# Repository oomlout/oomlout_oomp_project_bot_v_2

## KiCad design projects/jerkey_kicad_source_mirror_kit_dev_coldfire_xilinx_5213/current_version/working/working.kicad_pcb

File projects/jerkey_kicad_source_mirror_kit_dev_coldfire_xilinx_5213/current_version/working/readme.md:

# kicad_source_mirror
 
## summary 
* id: jerkey_kicad_source_mirror_kit_dev_coldfire_xilinx_5213
* user: jerkey
* name: kicad_source_mirror
* board: kit_dev_coldfire_xilinx_5213
* repo: https://github.com/jerkey/kicad-source-mirror
* src_file_repo_kicad_pcb: demos/kit-dev-coldfire-xilinx_5213/kit-dev-coldfire-xilinx_5213.kicad_pcb
* src_file_repo_kicad_pcb_link: https://github.com/jerkey/kicad-source-mirror/tree/master/demos/kit-dev-coldfire-xilinx_5213/kit-dev-coldfire-xilinx_5213.kicad_pcb

* src_file_repo_sch: demos/interf_u/interf_u.sch
* src_file_repo_sch_link: https://github.com/jerkey/kicad-source-mirror/tree/master/demos/interf_u/interf_u.sch
* full details link: https://github.com/oomlout/oomlout_oomp_project_bot_v_2/tree/main/projects/jerkey_kicad_source_mirror_kit_dev_coldfire_xilinx_5213/current_version/working

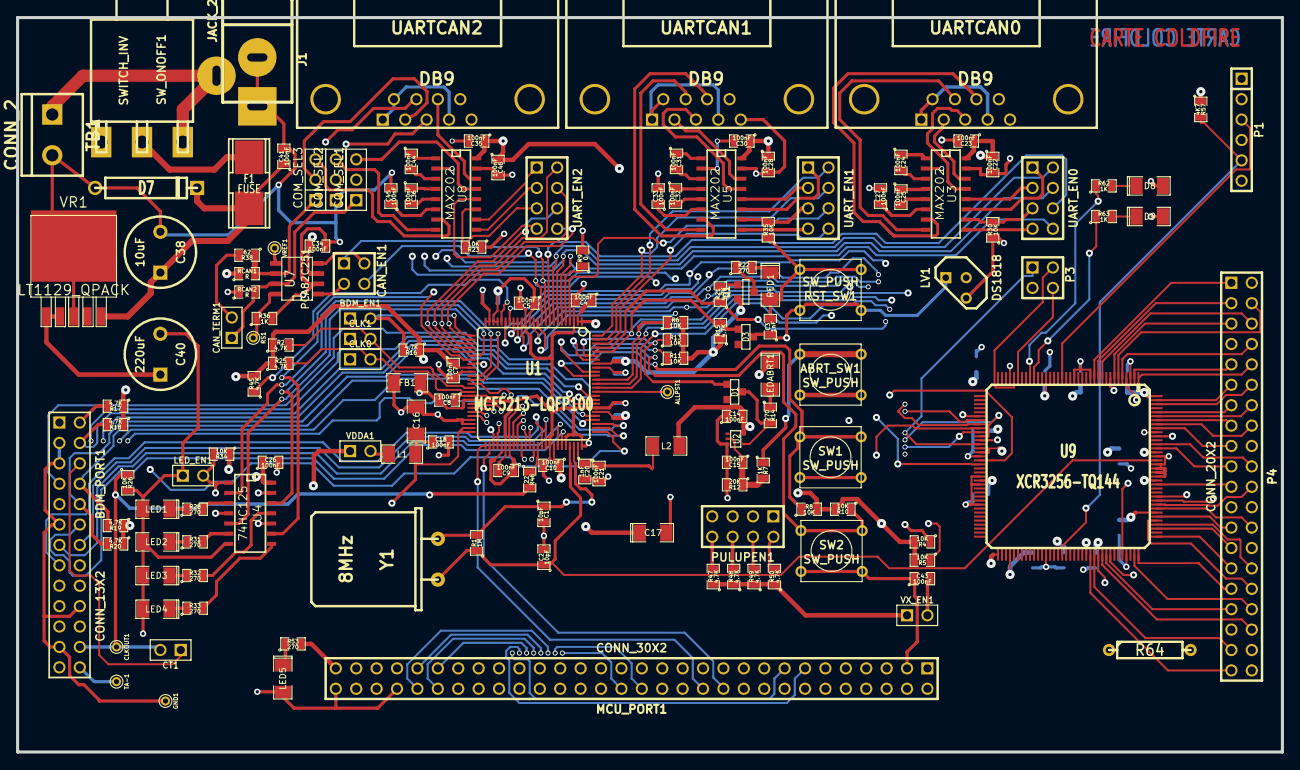
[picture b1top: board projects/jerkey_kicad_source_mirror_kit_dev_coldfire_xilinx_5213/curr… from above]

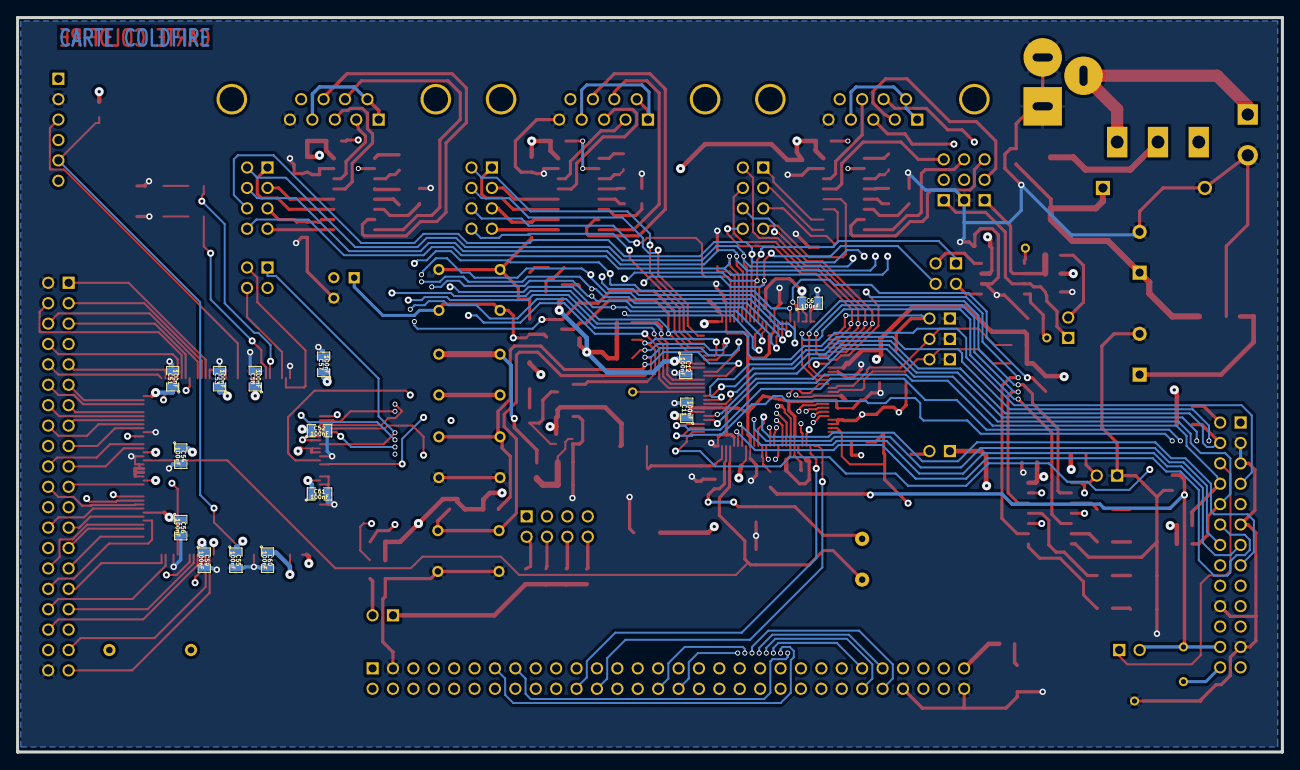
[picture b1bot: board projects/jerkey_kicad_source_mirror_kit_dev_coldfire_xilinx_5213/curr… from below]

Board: 4 copper layers, 157.5 x 91.4 mm, 162 parts (14 on the bottom side), 209 nets.

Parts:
ABRT_SW1: SW_PUSH; SW_PUSH_SMALL
ALLPST1: CONN_1; PINTST
BDM_EN1: JUMPER; PIN_ARRAY_2X1
BDM_PORT1: CONN_13X2; pin_array_13x2
C1, C2: 10pF; SM0805
C3, C20: 1nF; SM0805
C4, C5, C6, C7, C8, C9, C10, C11, C12, C14, C15, C18, C21, C22, C23, C24, C25, C26, C27, C28, C30, C31, C32, C33, C34, C35, C36, C41, C43, C44, C45, C46, C51, C52, C53, C54, C55, C56, C57, C58, C59, C60, C61: 100nF; SM0805
C16: 10uF; SM1206POL
C17: 100uF; SM1206POL
C38: 10uF; C2V8
C40: 220uF; C2V8
CAN_EN1: CONN_2X2; PIN_ARRAY_2X2
CAN_TERM1: JUMPER; PIN_ARRAY_2X1
CLK0, CLK1: JUMPER; PIN_ARRAY_2X1
CLKOUT1: CONN_1; PINTST
COM_SEL1, COM_SEL2, COM_SEL3: CONN_3; PIN_ARRAY_3X1
CT1: JUMPER; PIN_ARRAY_2X1
D1, D3: BAT54; ST23AK#1
D7: 1N4004; D5
D8, D9: LED; SM1206POL
F1: FUSE; FSUPCMS
FB1: BEAD; SM1206
GND1: CONN_1; PINTST
J1: JACK_2P; JACK_ALIM
L1, L2: 10uH; SM1206
LED1, LED2, LED3, LED4, LED5: LED; SM1206POL
LEDABRT1: RED; SM1206POL
LED_EN1: JUMPER; PIN_ARRAY_2X1
LV1: DS1818; TO92-INVERT
MCU_PORT1: CONN_30X2; PIN_ARRAY_30X2
P1: CONN_6; PIN_ARRAY-6X1
P3: CONN_2X2; PIN_ARRAY_2X2
P4: CONN_20X2; PIN_ARRAY_20X2
PULUPEN1: CONN_4X2; pin_array_4x2
Q1: 3906; SOT23EBC
R1: 1M; SM0805
R2, R15, R16, R17, R18, R19, R20, R21, R25, R45, R47, R48, R49, R50: 4,7K; SM0805
R4, R5, R6, R8, R10, R11, R13, R23, R26, R30, R34, R35: 10K; SM0805
R7, R36, R62, R63: 1K; SM0805
R9: 0; SM0805
R12: 20K; SM0805
R14, R22, R28, R31, R32, R33, R53: 270; SM0805
R38: 62; SM0805
R46: 22; SM0805
R57: 4K7; SM0805
R64: 3,3; R4
RCAN1, RCAN2: R; SM0805
RED1: LED_RESET1; SM1206POL
RS1: CONN_1; PINTST
RST_SW1: SW_PUSH; SW_PUSH_SMALL
SW1, SW2: SW_PUSH; SW_PUSH_SMALL
SW_ONOFF1: SWITCH_INV; SW_SPDT
TA-1: CONN_1; PINTST
TB1: CONN_2; bornier2
U1: MCF5213-LQFP100; VQFP100
U2: 74AHC1G14; SOT353
U3, U5, U8: MAX202; SO16E
U4: 74HC125; SO14E
U7: PCA82C251; SO8E
U9: XCR3256-TQ144; TQFP144
UARTCAN0, UARTCAN1, UARTCAN2: DB9; DB9FC
UART_EN0, UART_EN1, UART_EN2: CONN_4X2; pin_array_4x2
VDDA1: JUMPER; PIN_ARRAY_2X1
VR1: LT1129_QPACK; DPAK5
VREF1: CONN_1; PINTST
VX_EN1: JUMPER; PIN_ARRAY_2X1
Y1: 8MHz; HC-18UH

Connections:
/ALLPST: ALLPST1.1, U1.86
/AN0: MCU_PORT1.10, U1.43
/AN1: MCU_PORT1.12, U1.44
/AN2: MCU_PORT1.14, U1.45
/AN3: MCU_PORT1.16, U1.46
/AN4: MCU_PORT1.18, U1.54
/AN5: MCU_PORT1.20, U1.53
/AN6: MCU_PORT1.22, U1.52
/AN7: MCU_PORT1.24, U1.51
/BKPT-: BDM_PORT1.2, R17.2, U1.76
/CLKIN/EXTAL: C1.1, R1.2, U1.73, Y1.1
/CLKMOD0: CLK0.2, R25.2, U1.40
/CLKMOD1: CLK1.2, R2.2, U1.39
/DDAT0: BDM_PORT1.19, U1.77
/DDAT1: BDM_PORT1.18, U1.78
/DDAT2: BDM_PORT1.17, U1.83
/DDAT3: BDM_PORT1.16, U1.84
/DSCLK: BDM_PORT1.4, R18.2, U1.85
/DSI: BDM_PORT1.8, R19.2, U1.79
/DSO: BDM_PORT1.10, R20.2, U1.80
/DTIN0: MCU_PORT1.34, U1.36, U4.2
/DTIN1: MCU_PORT1.36, U1.37, U4.5
/DTIN2: MCU_PORT1.38, U1.31, U4.12
/DTIN3: MCU_PORT1.40, U1.32, U4.9
/GPT0: MCU_PORT1.49, U1.58
/GPT1: MCU_PORT1.50, U1.59
/GPT2: MCU_PORT1.51, U1.61
/GPT3: MCU_PORT1.52, U1.62
/IRQ-4: MCU_PORT1.33, R8.1, SW1.1, U1.90
/IRQ-5: MCU_PORT1.35, R10.1, SW2.1, U1.91
/IRQ-6: MCU_PORT1.37, R11.1, U1.94
/IRQ-7: D1.1, MCU_PORT1.39, R13.1, U1.95
/JTAG_EN: BDM_EN1.2, R16.2, U1.26
/PST0: BDM_PORT1.15, U1.65
/PST1: BDM_PORT1.14, U1.66
/PST2: BDM_PORT1.13, U1.69
/PST3: BDM_PORT1.12, U1.70
/QSPI_CS0: MCU_PORT1.23, PULUPEN1.3, U1.20
/QSPI_CS3: MCU_PORT1.29, U1.12
/TCLK: BDM_PORT1.24, CLKOUT1.1, CT1.2, R26.1, R46.2
/VDDPLL: C20.1, C21.1, L2.2, U1.74
/inout_user/CANRX: CAN_EN1.4, MCU_PORT1.28, PULUPEN1.7, U1.11
/inout_user/CANTX: CAN_EN1.1, MCU_PORT1.26, PULUPEN1.5, U1.10
/inout_user/CAN_H: CAN_TERM1.1, COM_SEL1.1, RCAN2.2, U7.7
/inout_user/CAN_L: COM_SEL3.1, R38.1, RCAN1.2, U7.6
/inout_user/CTS0: U3.8, UARTCAN0.7
/inout_user/CTS1: U5.8, UARTCAN1.7
/inout_user/CTS2/CANH: COM_SEL1.2, UARTCAN2.7
/inout_user/PWM1: MCU_PORT1.13, U1.38
/inout_user/PWM3: MCU_PORT1.15, U1.33
/inout_user/PWM5: MCU_PORT1.30, U1.60
/inout_user/PWM7: MCU_PORT1.32, U1.63
/inout_user/QSPI_DIN: MCU_PORT1.19, U1.16, U9.46
/inout_user/QSPI_DOUT: MCU_PORT1.17, U1.17, U9.47
/inout_user/QSPI_SCLK: MCU_PORT1.21, PULUPEN1.1, U1.18, U9.48
/inout_user/RCON-: MCU_PORT1.53, R45.1, U1.21
/inout_user/RSTI-: BDM_PORT1.7, D3.1, MCU_PORT1.6, R15.2, U1.96
/inout_user/RTS0: U3.7, UARTCAN0.8
/inout_user/RTS0-: MCU_PORT1.4, R21.1, U1.97
/inout_user/RTS1: U5.7, UARTCAN1.8
/inout_user/RTS2: U8.14, UARTCAN2.8
/inout_user/RXD0: U3.13, UARTCAN0.3
/inout_user/RXD1: U5.13, UARTCAN1.3
/inout_user/RXD2: COM_SEL2.2, UARTCAN2.3
/inout_user/RxD_CAN: CAN_EN1.2, U7.4
/inout_user/TXD0: U3.14, UARTCAN0.2
/inout_user/TXD1: U5.14, UARTCAN1.2
/inout_user/TXD2/CANL: COM_SEL3.2, UARTCAN2.2
/inout_user/TxD_CAN: CAN_EN1.3, U7.1
/inout_user/UCTS0: MCU_PORT1.44, U1.6, UART_EN0.8
/inout_user/UCTS1: MCU_PORT1.11, P3.1, U1.98, U9.49, UART_EN1.8
/inout_user/UCTS2: MCU_PORT1.48, U1.27, UART_EN2.8
/inout_user/URTS0: MCU_PORT1.42, U1.9, UART_EN0.6
/inout_user/URTS1: MCU_PORT1.9, P3.3, U1.4, U9.53, UART_EN1.6
/inout_user/URTS2: MCU_PORT1.46, U1.30, UART_EN2.6
/inout_user/URXD0: MCU_PORT1.43, U1.7, UART_EN0.4
/inout_user/URXD1: MCU_PORT1.7, U1.100, UART_EN1.4
/inout_user/URXD2: MCU_PORT1.47, U1.28, UART_EN2.4
/inout_user/UTXD0: MCU_PORT1.41, U1.8, UART_EN0.2
/inout_user/UTXD1: MCU_PORT1.5, U1.99, UART_EN1.2
/inout_user/UTXD2: MCU_PORT1.45, U1.29, UART_EN2.2
/inout_user/VCCA: C16.1, C18.1, L1.2, MCU_PORT1.55, MCU_PORT1.57, U1.49, U1.50
/xilinx/+3,3V_OUT: P4.38, R64.2
/xilinx/GLCK2: C2.1, R1.1, U1.72, U9.128, Y1.2
/xilinx/IRQ-1: MCU_PORT1.2, R4.1, U1.87, U9.42
/xilinx/IRQ-2: MCU_PORT1.8, R5.1, U1.88, U9.43
/xilinx/IRQ-3: MCU_PORT1.31, R6.1, U1.89, U9.44
/xilinx/LED_TEST1: R62.1, U9.28
/xilinx/LED_TEST2: R63.1, U9.27
/xilinx/QSPI_CS1: MCU_PORT1.25, U1.19, U9.54
/xilinx/QSPI_CS2: MCU_PORT1.27, U1.13, U9.45
/xilinx/TCK: P1.5, R57.2, U9.89
/xilinx/TDI: P1.4, U9.4
/xilinx/TDO: P1.6, U9.104
/xilinx/TMS: P1.3, U9.20
/xilinx/XIL_D0: P4.1, U9.12
/xilinx/XIL_D1: P4.3, U9.11
/xilinx/XIL_D2: P4.5, U9.7
/xilinx/XIL_D3: P4.7, U9.8
/xilinx/XIL_D4: P4.9, U9.2
/xilinx/XIL_D5: P4.11, U9.143
/xilinx/XIL_D6: P4.13, U9.140
/xilinx/XIL_D7: P4.15, U9.138
/xilinx/XIL_D8: P4.17, U9.136
/xilinx/XIL_D9: P4.19, U9.131
/xilinx/XIL_D10: P4.21, U9.122
/xilinx/XIL_D11: P4.23, U9.119
/xilinx/XIL_D12: P4.25, U9.114
/xilinx/XIL_D13: P4.27, U9.111
/xilinx/XIL_D14: P4.29, U9.109
/xilinx/XIL_D15: P4.31, U9.108
/xilinx/XIL_D16: P4.33, U9.100
/xilinx/XIL_D17: P4.35, U9.101
/xilinx/XIL_D18: P4.37, U9.97
/xilinx/XIL_D19: P4.39, U9.96
/xilinx/XIL_D20: P4.4, U9.6
/xilinx/XIL_D21: P4.6, U9.10
/xilinx/XIL_D22: P4.8, U9.5
/xilinx/XIL_D23: P4.10, U9.1
/xilinx/XIL_D24: P4.12, U9.142
/xilinx/XIL_D25: P4.14, U9.139
/xilinx/XIL_D26: P4.16, U9.137
/xilinx/XIL_D27: P4.18, U9.134
/xilinx/XIL_D28: P4.20, U9.132
/xilinx/XIL_D29: P4.22, U9.117
/xilinx/XIL_D30: P4.24, U9.118
/xilinx/XIL_D31: P4.26, U9.116
/xilinx/XIL_D32: P4.28, U9.98
/xilinx/XIL_D33: P4.30, U9.112
/xilinx/XIL_D34: P4.32, U9.113
/xilinx/XIL_D35: P4.34, U9.107
/xilinx/XIL_D36: P4.36, U9.99
GND: BDM_EN1.1, BDM_PORT1.3, BDM_PORT1.5, BDM_PORT1.11, BDM_PORT1.20, BDM_PORT1.23, C1.2, C2.2, C3.2, C4.2, C5.2, C6.2, C7.2, C8.2, C9.2, C10.2, C11.2, C12.2, C14.1, C15.2, C17.2, C20.2, C21.2, C22.2, C26.2, C27.2, C28.2, C33.2, C34.2, C38.2, C40.2, C41.2, C43.1, C45.2, C46.2, C51.2, C52.2, C53.2, C54.2, C55.2, C56.2, C57.2, C58.2, C59.2, C60.2, C61.2, CLK0.1, CLK1.1, COM_SEL2.1, D7.1, D8.2, D9.2, FB1.1, GND1.1, J1.1, J1.2, LED1.2, LED2.2, LED3.2, LED4.2, LED5.2, LED_EN1.1, LV1.3, MCU_PORT1.3, MCU_PORT1.54, MCU_PORT1.60, P1.2, P4.2, P4.40, R9.2, R12.2, R23.1, R26.2, R30.1, R35.1, R36.2, RCAN2.1, RED1.2, RST_SW1.2, SW1.2, SW2.2, TB1.2, U1.3, U1.15, U1.24, U1.25, U1.35, U1.42, U1.56, U1.67, U1.71, U1.75, U1.82, U1.92, U2.3, U3.15, U4.7, U5.15, U7.2, U8.15, U9.3, U9.13, U9.17, U9.33, U9.52, U9.57, U9.59, U9.64, U9.85, U9.105, U9.124, U9.125, U9.126, U9.127, U9.129, U9.135, UARTCAN0.5, UARTCAN1.5, UARTCAN2.5, VR1.3
GNDA: C16.2, C18.2, FB1.2, MCU_PORT1.56, MCU_PORT1.58, U1.47, U1.48
unnamed: ABRT_SW1.1, R7.1
unnamed: BDM_PORT1.6, CT1.1
unnamed: BDM_PORT1.26, TA-1.1
unnamed: C3.1, D3.2, LV1.1, RST_SW1.1
unnamed: C15.1, R7.2, R12.1, U2.2
unnamed: C23.2, U3.2
unnamed: C24.1, U3.1
unnamed: C24.2, U3.3
unnamed: C25.1, U3.4
unnamed: C25.2, U3.5
unnamed: C27.1, U3.6
unnamed: C30.2, U5.2
unnamed: C31.1, U5.1
unnamed: C31.2, U5.3
unnamed: C32.1, U5.4
unnamed: C32.2, U5.5
unnamed: C33.1, U5.6
unnamed: C35.2, U8.2
unnamed: C36.1, U8.4
unnamed: C36.2, U8.5
unnamed: C38.1, C41.1, D7.2, F1.2, VR1.5
unnamed: C43.2, MCU_PORT1.1, VX_EN1.2
unnamed: C44.1, U8.1
unnamed: C44.2, U8.3
unnamed: C45.1, U8.6
unnamed: CAN_TERM1.2, R38.2
unnamed: COM_SEL1.3, U8.13
unnamed: COM_SEL2.3, U8.8
unnamed: COM_SEL3.3, U8.7
unnamed: D1.2, R14.2, U2.4
unnamed: D8.1, R62.2
unnamed: D9.1, R63.2
unnamed: F1.1, SW_ONOFF1.2
unnamed: J1.3, SW_ONOFF1.3, TB1.1
unnamed: L1.1, VDDA1.2
unnamed: LED1.1, R28.1
unnamed: LED2.1, R31.1
unnamed: LED3.1, R32.1
unnamed: LED4.1, R33.1
unnamed: LED5.1, R53.1
unnamed: LEDABRT1.2, R14.1
unnamed: LED_EN1.2, R34.2, U4.1, U4.4, U4.10, U4.13
unnamed: P3.2, U9.32
unnamed: P3.4, U9.31
unnamed: PULUPEN1.2, R50.2
unnamed: PULUPEN1.4, R49.2
unnamed: PULUPEN1.6, R48.2
unnamed: PULUPEN1.8, R47.2
unnamed: Q1.2, R21.2
unnamed: Q1.3, R22.1
unnamed: R9.1, U1.5
unnamed: R22.2, RED1.1
unnamed: R23.2, U8.11, UART_EN2.5
unnamed: R28.2, U4.3
unnamed: R30.2, U3.10, UART_EN0.5
unnamed: R31.2, U4.6
unnamed: R32.2, U4.11
unnamed: R33.2, U4.8
unnamed: R35.2, U5.10, UART_EN1.5
unnamed: R36.1, RS1.1, U7.8
unnamed: R46.1, U1.64
unnamed: U3.9, UART_EN0.7
unnamed: U3.11, UART_EN0.1
unnamed: U3.12, UART_EN0.3
unnamed: U5.9, UART_EN1.7
unnamed: U5.11, UART_EN1.1
unnamed: U5.12, UART_EN1.3
unnamed: U7.5, VREF1.1
unnamed: U8.9, UART_EN2.3
unnamed: U8.10, UART_EN2.1
unnamed: U8.12, UART_EN2.7
unnamed: UARTCAN0.1, UARTCAN0.4, UARTCAN0.6
unnamed: UARTCAN1.1, UARTCAN1.4, UARTCAN1.6
unnamed: UARTCAN2.1, UARTCAN2.4, UARTCAN2.6
VDD: ABRT_SW1.2, BDM_PORT1.9, BDM_PORT1.25, C4.1, C5.1, C6.1, C7.1, C8.1, C9.1, C10.1, C11.1, C12.1, C14.2, C17.1, C22.1, C23.1, C26.1, C28.1, C30.1, C34.1, C35.1, C40.1, C46.1, C51.1, C52.1, C53.1, C54.1, C55.1, C56.1, C57.1, C58.1, C59.1, C60.1, C61.1, L2.1, LEDABRT1.1, LV1.2, MCU_PORT1.59, P1.1, Q1.1, R2.1, R4.2, R5.2, R6.2, R8.2, R10.2, R11.2, R13.2, R15.1, R16.1, R17.1, R18.1, R19.1, R20.1, R25.1, R34.1, R45.2, R47.1, R48.1, R49.1, R50.1, R53.2, R57.1, R64.1, RCAN1.1, U1.1, U1.2, U1.14, U1.22, U1.23, U1.34, U1.41, U1.55, U1.57, U1.68, U1.81, U1.93, U2.5, U3.16, U4.14, U5.16, U7.3, U8.16, U9.24, U9.50, U9.51, U9.58, U9.73, U9.76, U9.95, U9.115, U9.123, U9.130, U9.144, VDDA1.1, VR1.1, VR1.2, VX_EN1.1

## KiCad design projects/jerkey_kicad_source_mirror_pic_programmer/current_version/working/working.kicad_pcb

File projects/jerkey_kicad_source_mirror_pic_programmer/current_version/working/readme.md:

# kicad_source_mirror
 
## summary 
* id: jerkey_kicad_source_mirror_pic_programmer
* user: jerkey
* name: kicad_source_mirror
* board: pic_programmer
* repo: https://github.com/jerkey/kicad-source-mirror
* src_file_repo_kicad_pcb: demos/pic_programmer/pic_programmer.kicad_pcb
* src_file_repo_kicad_pcb_link: https://github.com/jerkey/kicad-source-mirror/tree/master/demos/pic_programmer/pic_programmer.kicad_pcb

* src_file_repo_sch: demos/pic_programmer/pic_programmer.sch
* src_file_repo_sch_link: https://github.com/jerkey/kicad-source-mirror/tree/master/demos/pic_programmer/pic_programmer.sch
* full details link: https://github.com/oomlout/oomlout_oomp_project_bot_v_2/tree/main/projects/jerkey_kicad_source_mirror_pic_programmer/current_version/working

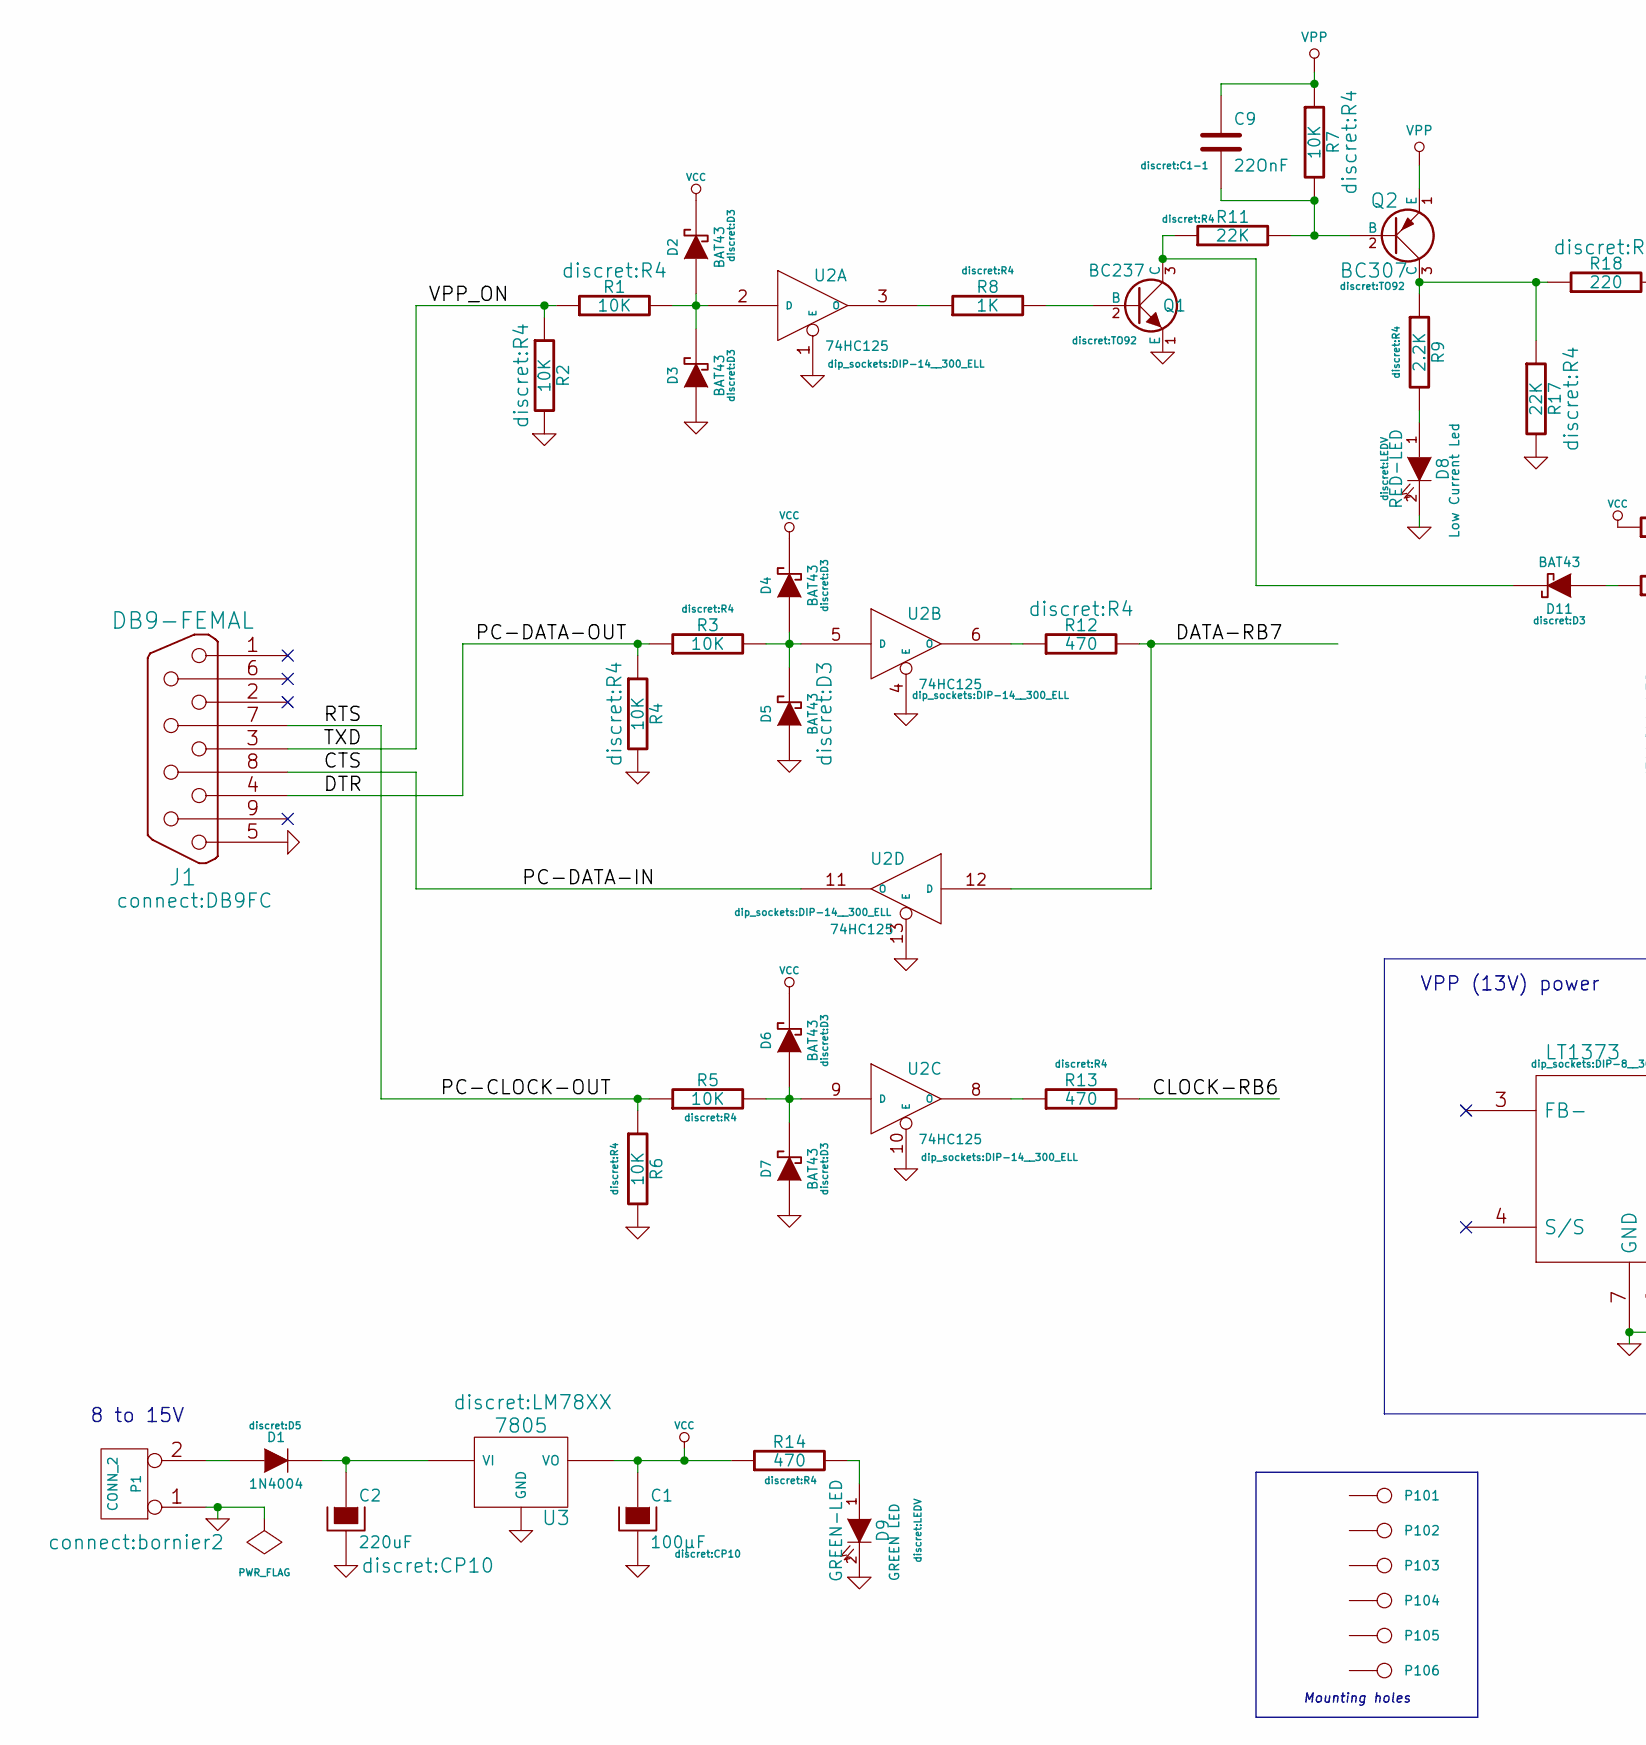
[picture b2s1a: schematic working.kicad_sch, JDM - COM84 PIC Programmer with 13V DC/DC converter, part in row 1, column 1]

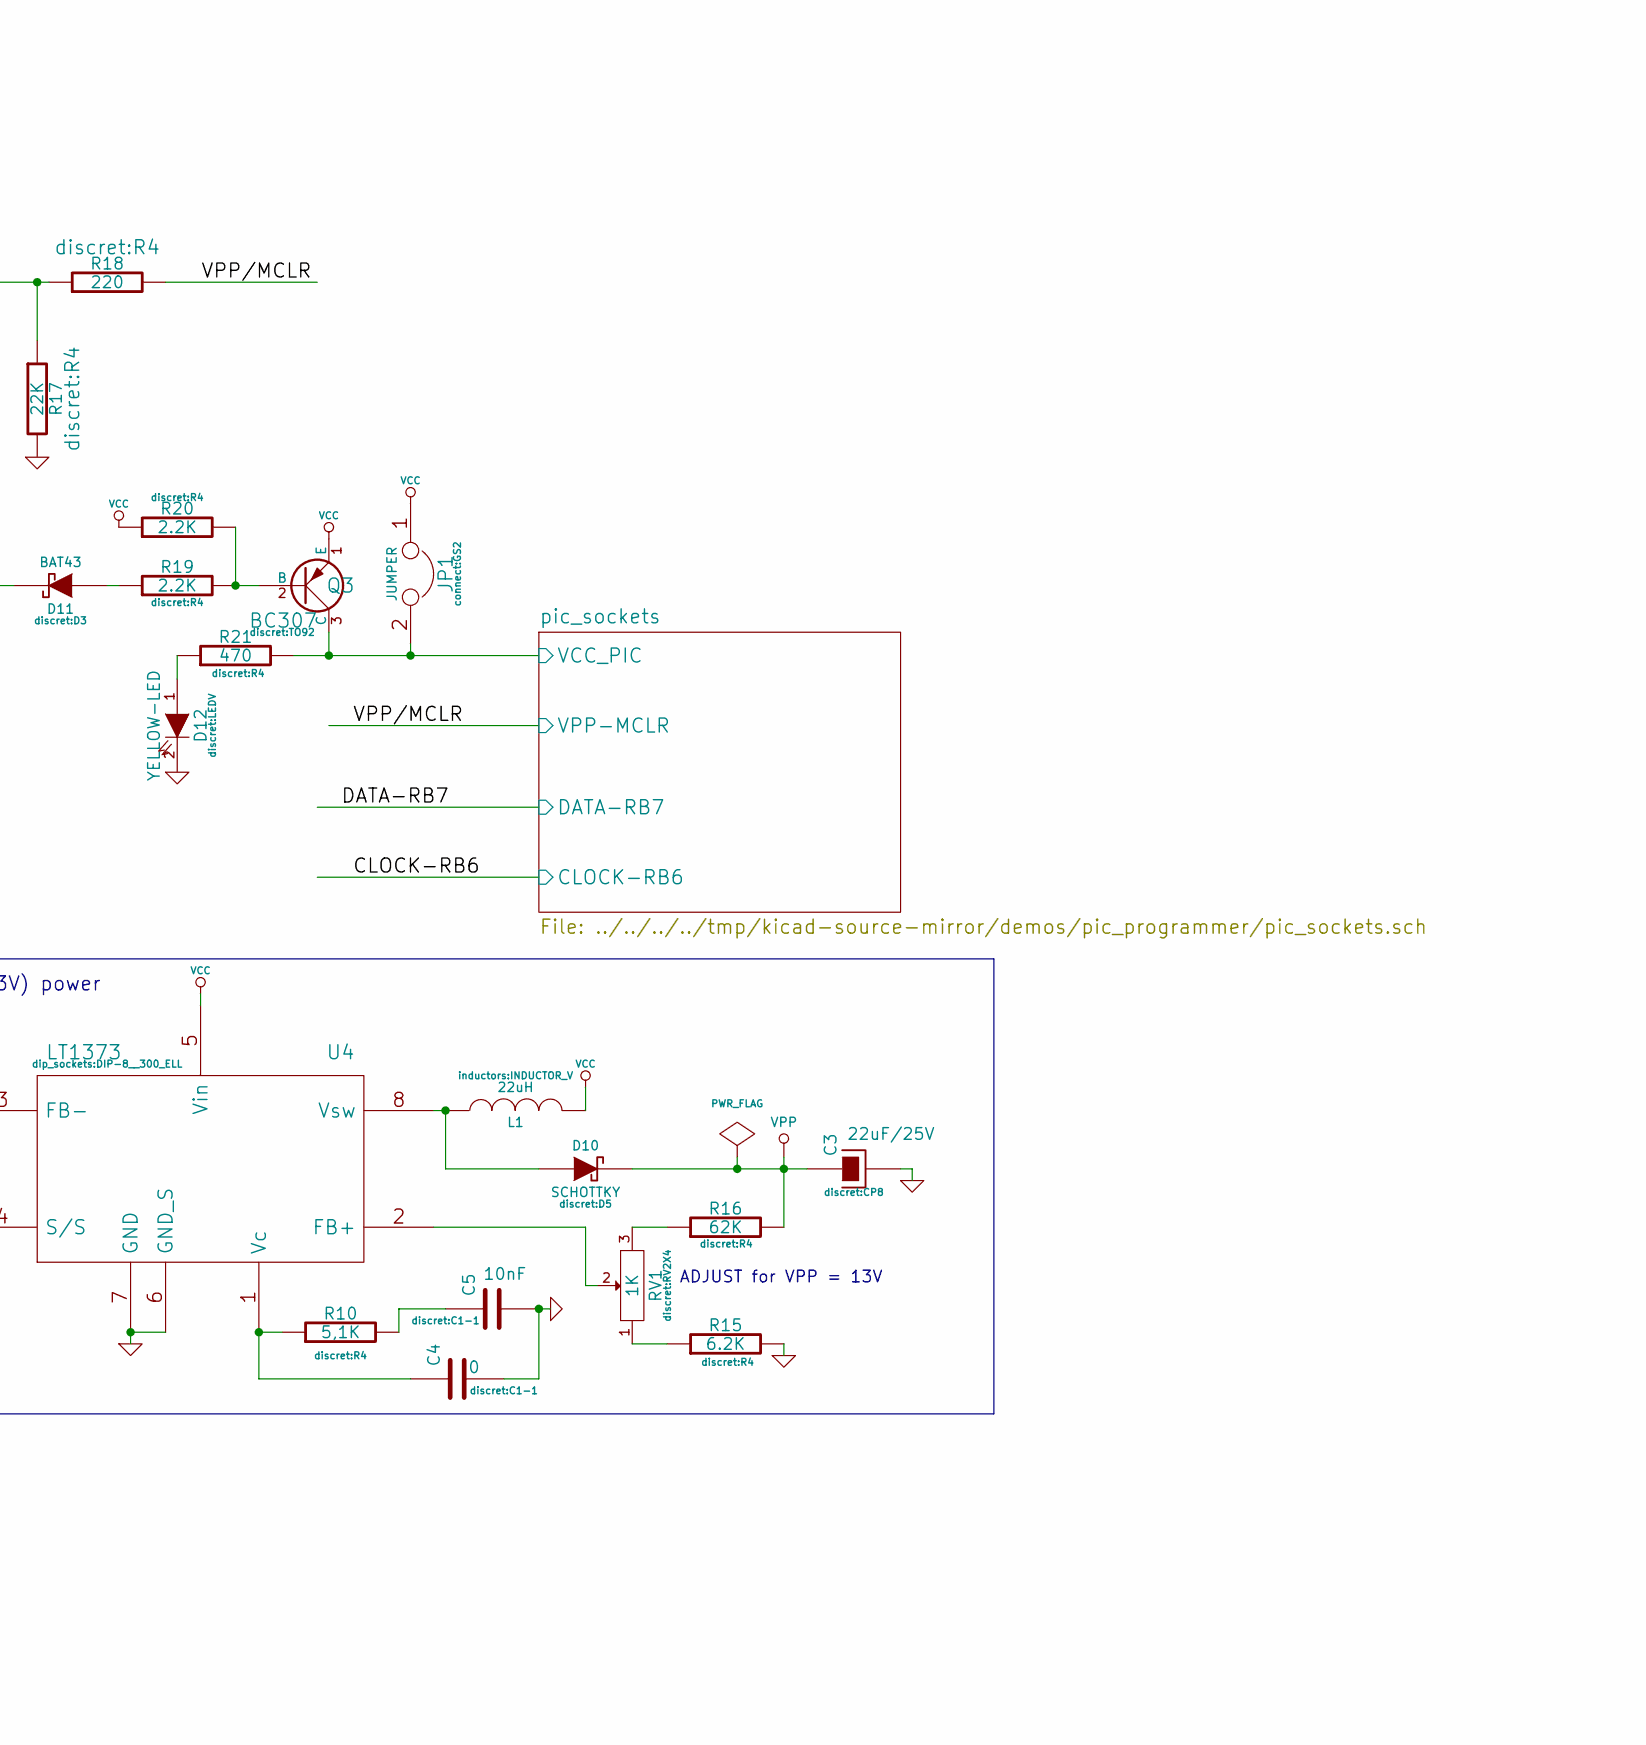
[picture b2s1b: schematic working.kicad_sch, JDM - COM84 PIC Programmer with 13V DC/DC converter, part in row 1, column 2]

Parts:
C1: 100µF; CP10
C2: 220uF; CP10
C3: 22uF/25V; CP8
C4: 0; C1-1
C5: 10nF; C1-1
C9: 22OnF; C1-1
D1: 1N4004; D5
D2, D3, D4, D5, D6, D7, D11: BAT43; D3
D8: RED-LED; LEDV
D9: GREEN-LED; LEDV
D10: SCHOTTKY; D5
D12: YELLOW-LED; LEDV
J1: DB9-FEMAL; DB9FC
JP1: JUMPER; GS2
L1: 22uH; INDUCTOR_V
P1: CONN_2; bornier2
P101, P102, P103, P104, P105, P106: CONN_1; 1pin-4
Q1: BC237; TO92
Q2, Q3: BC307; TO92
R1, R2, R3, R4, R5, R6, R7: 10K; R4
R8: 1K; R4
R9, R19, R20: 2.2K; R4
R10: 5,1K; R4
R11, R17: 22K; R4
R12, R13, R14, R21: 470; R4
R15: 6.2K; R4
R16: 62K; R4
R18: 220; R4
RV1: 1K; RV2X4
U2: 74HC125; DIP-14__300_ELL
U3: 7805; LM78XX
U4: LT1373; DIP-8__300_ELL

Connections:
/CTS: J1.8, U2.11 (O)
/DTR: J1.4, R3.1, R4.1
/PC-CLOCK-OUT: J1.7, R5.1, R6.1
/TXD: J1.3, R1.1, R2.1
/pic_sockets/CLOCK-RB6: R13.2; also elsewhere on the board
/pic_sockets/DATA-RB7: R12.2, U2.12 (D); also elsewhere on the board
/pic_sockets/VCC_PIC: JP1.2, Q3.3 (C), R21.2; also elsewhere on the board
/pic_sockets/VPP-MCLR: R18.2; also elsewhere on the board
GND: C1.2, C2.2, C3.2, C4.2, C5.2, D3.1 (A), D5.1 (A), D7.1 (A), D8.2 (K), D9.2 (K), D12.2 (K), J1.5, P1.1, Q1.1 (E), R2.2, R4.2, R6.2, R15.2, R17.2, U2.1 (E), U2.4 (E), U2.7 (GND), U2.10 (E), U2.13 (E), U3.GND, U4.6 (GND_S), U4.7 (GND); also elsewhere on the board
unnamed: C2.1, D1.2 (K), U3.VI
unnamed: C4.1, R10.1, U4.1 (Vc)
unnamed: C5.1, R10.2
unnamed: C9.2, Q2.2 (B), R7.2, R11.2
unnamed: D1.1 (A), P1.2 (PM)
unnamed: D2.1 (A), D3.2 (K), R1.2, U2.2 (D)
unnamed: D4.1 (A), D5.2 (K), R3.2, U2.5 (D)
unnamed: D6.1 (A), D7.2 (K), R5.2, U2.9 (D)
unnamed: D8.1 (A), R9.2
unnamed: D9.1 (A), R14.2
unnamed: D10.1 (A), L1.1, U4.8 (Vsw)
unnamed: D11.1 (A), R19.1
unnamed: D11.2 (K), Q1.3 (C), R11.1
unnamed: D12.1 (A), R21.1
unnamed: Q1.2 (B), R8.2
unnamed: Q2.3 (C), R9.1, R17.1, R18.1
unnamed: Q3.2 (B), R19.2, R20.2
unnamed: R8.1, U2.3 (O)
unnamed: R12.1, U2.6 (O)
unnamed: R13.1, U2.8 (O)
unnamed: R15.1, RV1.1
unnamed: R16.1, RV1.3
unnamed: RV1.2, U4.2 (FB+)
VCC: C1.1, D2.2 (K), D4.2 (K), D6.2 (K), JP1.1, L1.2, Q3.1 (E), R14.1, R20.1, U2.14 (VCC), U3.VO, U4.5 (Vin)
VPP: C3.1, C9.1, D10.2 (K), Q2.1 (E), R7.1, R16.2

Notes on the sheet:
VPP (13V) power
8 to 15V
ADJUST for VPP = 13V
Mounting holes

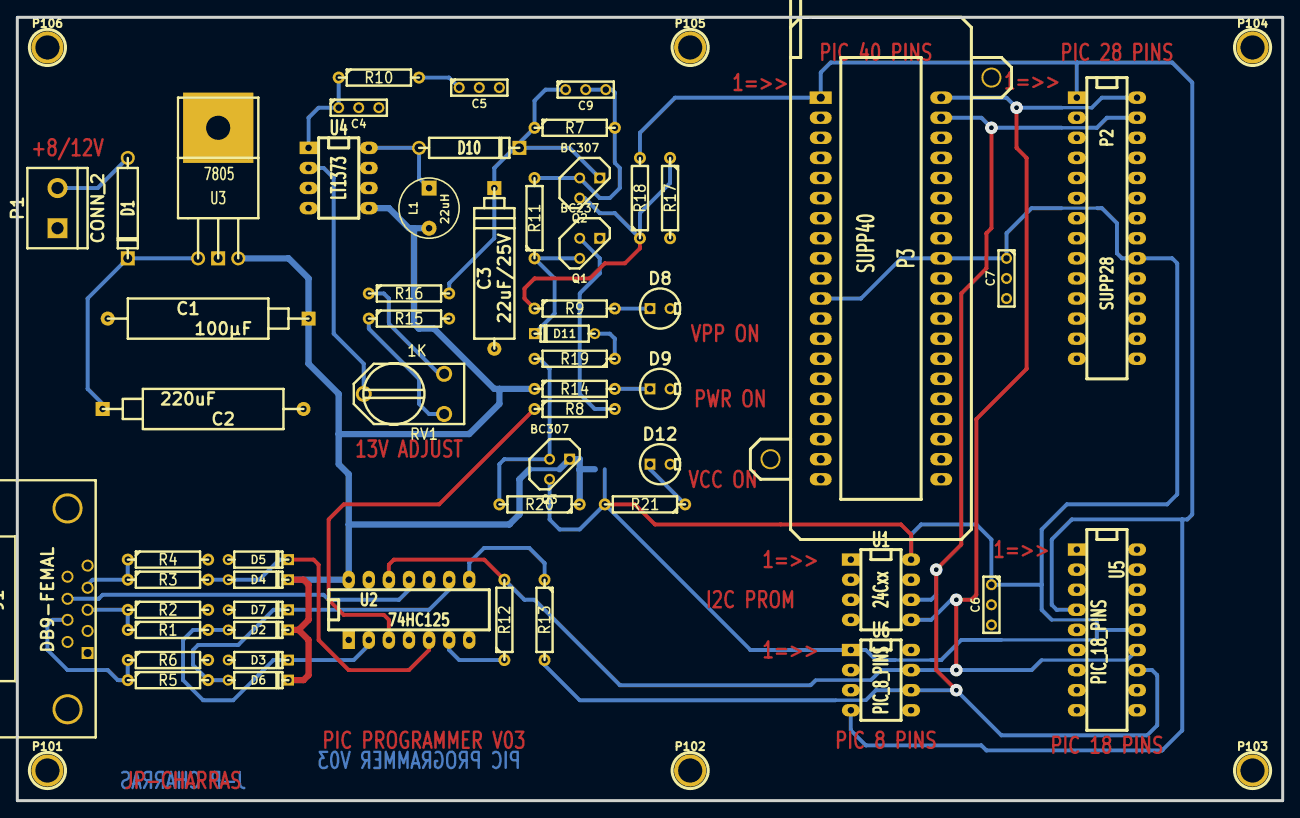
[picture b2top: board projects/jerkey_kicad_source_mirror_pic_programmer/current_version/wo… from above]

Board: 2 copper layers, 160.0 x 99.1 mm, 63 parts (1 on the bottom side), 34 nets.

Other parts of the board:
C6, C7: 100nF; C1-1
P2: SUPP28; DIP-28__300_ELL
P3: SUPP40; 40tex-Ell600
U1: 24Cxx; DIP-8__300_ELL
U5: PIC_18_PINS; DIP-18__300_ELL
U6: PIC_8_PINS; DIP-8__300_ELL

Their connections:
/pic_sockets/CLOCK-RB6: P2.27, P3.39, U1.6, U5.12, U6.6; also elsewhere on the board
/pic_sockets/DATA-RB7: P2.28, P3.40, U1.5, U5.13, U6.7; also elsewhere on the board
/pic_sockets/VCC_PIC: C6.1, C7.1, P2.20, P3.11, P3.32, U1.8, U5.14, U6.1; also elsewhere on the board
/pic_sockets/VPP-MCLR: P2.1, P3.1, U5.4, U6.4; also elsewhere on the board
GND: C6.2, C7.2, P2.8, P2.19, P3.8, P3.12, P3.31, U1.1, U1.2, U1.3, U1.4, U5.5, U6.8; also elsewhere on the board

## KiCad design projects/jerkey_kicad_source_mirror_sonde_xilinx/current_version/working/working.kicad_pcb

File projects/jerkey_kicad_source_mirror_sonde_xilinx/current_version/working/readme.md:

# kicad_source_mirror
 
## summary 
* id: jerkey_kicad_source_mirror_sonde_xilinx
* user: jerkey
* name: kicad_source_mirror
* board: sonde_xilinx
* repo: https://github.com/jerkey/kicad-source-mirror
* src_file_repo_kicad_pcb: demos/sonde xilinx/sonde xilinx.kicad_pcb
* src_file_repo_kicad_pcb_link: https://github.com/jerkey/kicad-source-mirror/tree/master/demos/sonde xilinx/sonde xilinx.kicad_pcb

* src_file_repo_sch: demos/sonde xilinx/sonde xilinx.sch
* src_file_repo_sch_link: https://github.com/jerkey/kicad-source-mirror/tree/master/demos/sonde xilinx/sonde xilinx.sch
* full details link: https://github.com/oomlout/oomlout_oomp_project_bot_v_2/tree/main/projects/jerkey_kicad_source_mirror_sonde_xilinx/current_version/working

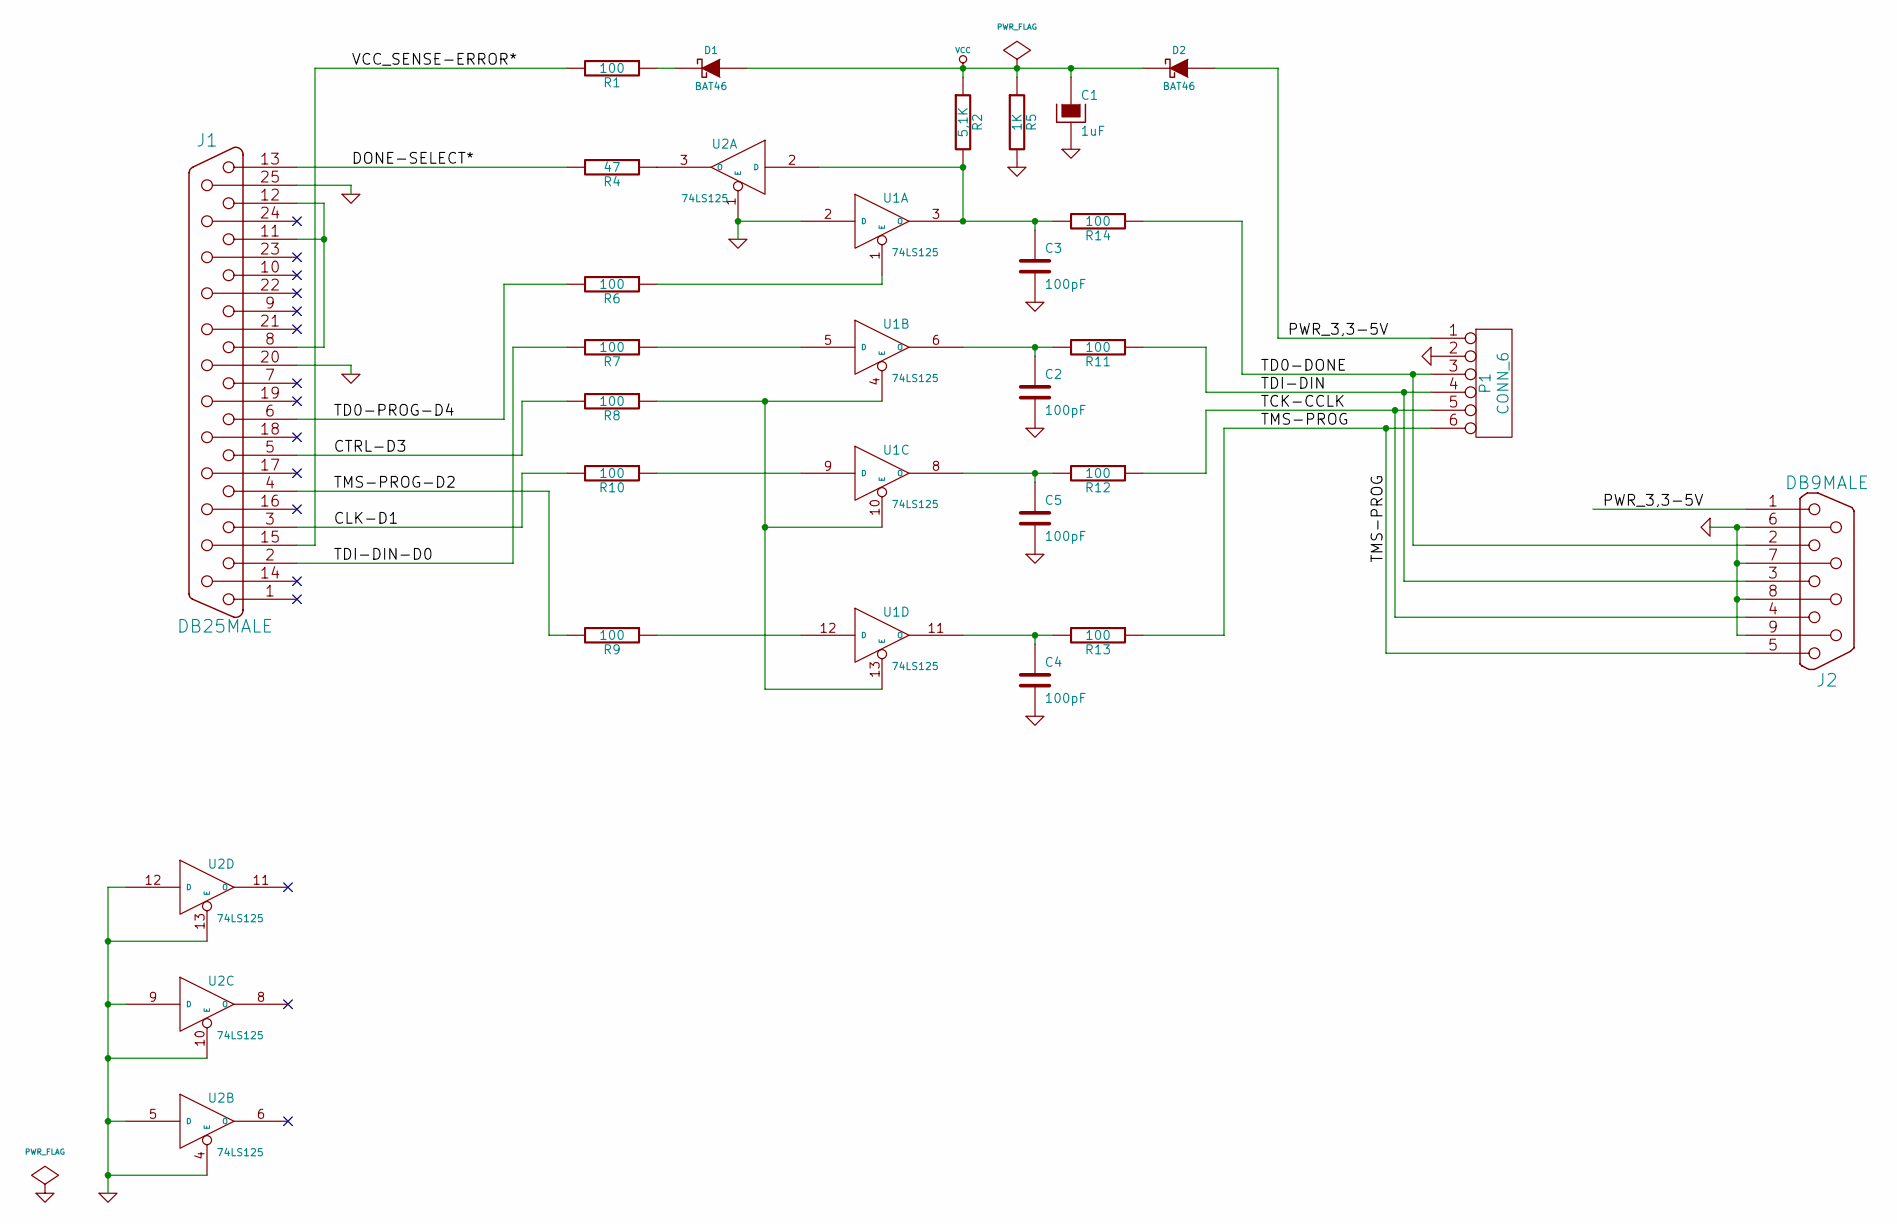
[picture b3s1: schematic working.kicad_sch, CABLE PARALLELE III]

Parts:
C1: 1uF
C2, C3, C4, C5: 100pF
D1, D2: BAT46
J1: DB25MALE
J2: DB9MALE
P1: CONN_6
R1, R6, R7, R8, R9, R10, R11, R12, R13, R14: 100
R2: 5,1K
R4: 47
R5: 1K
U1, U2: 74LS125

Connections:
/CLK-D1: J1.3, R10.2
/CTRL-D3: J1.5, R8.2
/DONE-SELECT*: J1.13, R4.2
/PWR_3,3-5V: D2.1 (A), J2.1, P1.1
/TCK-CCLK: J2.4, P1.5, R12.1
/TD0-DONE: J2.2, P1.3, R14.1
/TD0-PROG-D4: J1.6, R6.2
/TDI-DIN: J2.3, P1.4, R11.1
/TDI-DIN-D0: J1.2, R7.2
/TMS-PROG: J2.5, P1.6, R13.1
/TMS-PROG-D2: J1.4, R9.2
/VCC_SENSE-ERROR*: J1.15, R1.2
GND: C1.2, C2.2, C3.2, C4.2, C5.2, J1.20, J1.25, J2.6, J2.7, J2.8, J2.9, P1.2, R5.2, U1.2 (D), U1.7 (GND), U2.1 (E), U2.4 (E), U2.5 (D), U2.7 (GND), U2.9 (D), U2.10 (E), U2.12 (D), U2.13 (E)
unnamed: J1.8, J1.11, J1.12
unnamed: D1.2 (K), R1.1
unnamed: R4.1, U2.3 (O)
unnamed: R7.1, U1.5 (D)
unnamed: R10.1, U1.9 (D)
unnamed: R6.1, U1.1 (E)
unnamed: R9.1, U1.12 (D)
unnamed: R8.1, U1.4 (E), U1.10 (E), U1.13 (E)
unnamed: C4.1, R13.2, U1.11 (O)
unnamed: C2.1, R11.2, U1.6 (O)
unnamed: C5.1, R12.2, U1.8 (O)
unnamed: C3.1, R2.2, R14.2, U1.3 (O), U2.2 (D)
VCC: C1.1, D1.1 (A), D2.2 (K), R2.1, R5.1, U1.14 (VCC), U2.14 (VCC)

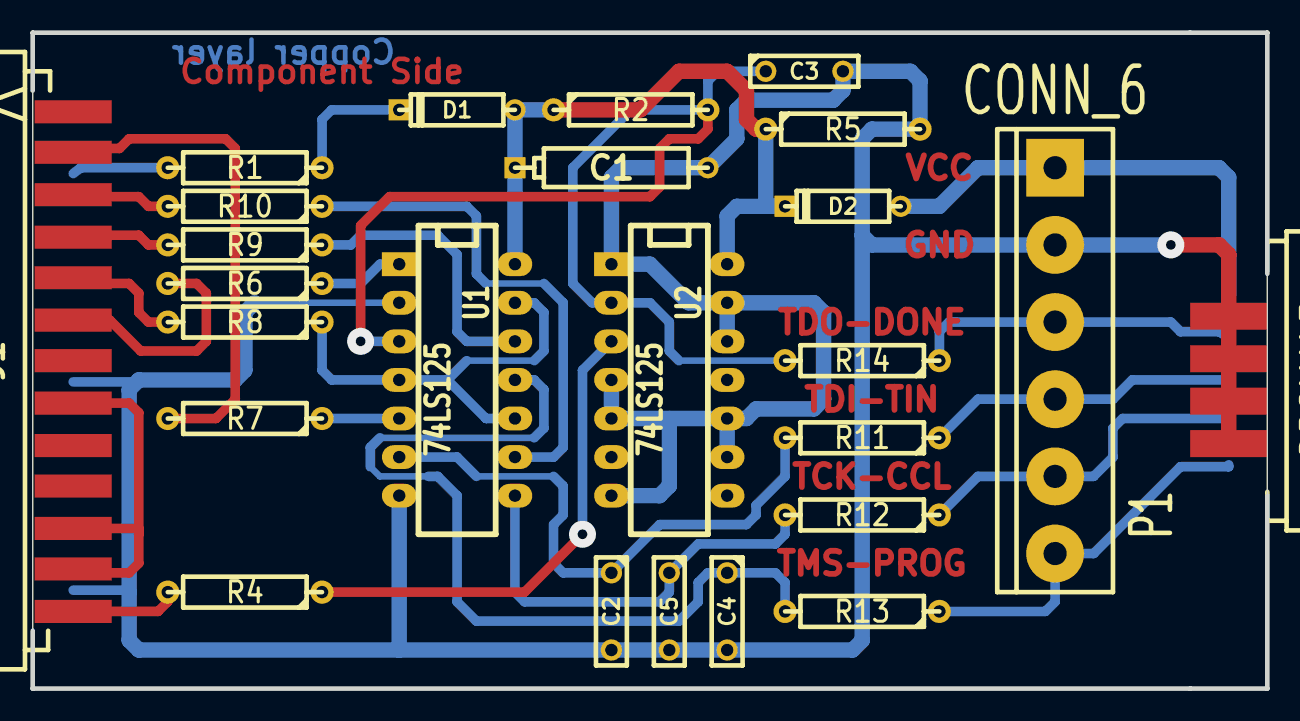
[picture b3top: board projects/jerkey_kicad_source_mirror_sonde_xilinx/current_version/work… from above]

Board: 2 copper layers, 81.3 x 43.2 mm, 25 parts (0 on the bottom side), 26 nets.

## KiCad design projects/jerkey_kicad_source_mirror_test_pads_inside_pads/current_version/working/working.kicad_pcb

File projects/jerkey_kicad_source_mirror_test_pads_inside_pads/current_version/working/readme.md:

# kicad_source_mirror
 
## summary 
* id: jerkey_kicad_source_mirror_test_pads_inside_pads
* user: jerkey
* name: kicad_source_mirror
* board: test_pads_inside_pads
* repo: https://github.com/jerkey/kicad-source-mirror
* src_file_repo_kicad_pcb: demos/test_pads_inside_pads/test_pads_inside_pads.kicad_pcb
* src_file_repo_kicad_pcb_link: https://github.com/jerkey/kicad-source-mirror/tree/master/demos/test_pads_inside_pads/test_pads_inside_pads.kicad_pcb

* src_file_repo_sch: demos/test_pads_inside_pads/test_pads_inside_pads.sch
* src_file_repo_sch_link: https://github.com/jerkey/kicad-source-mirror/tree/master/demos/test_pads_inside_pads/test_pads_inside_pads.sch
* full details link: https://github.com/oomlout/oomlout_oomp_project_bot_v_2/tree/main/projects/jerkey_kicad_source_mirror_test_pads_inside_pads/current_version/working

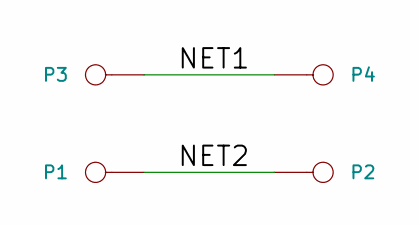
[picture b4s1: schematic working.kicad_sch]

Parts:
P1, P2, P3, P4: CONN_1

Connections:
/NET1: P3.1, P4.1
/NET2: P1.1, P2.1

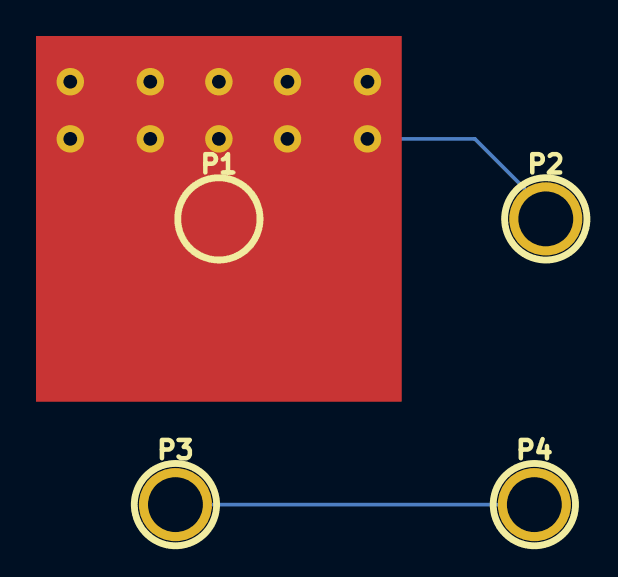
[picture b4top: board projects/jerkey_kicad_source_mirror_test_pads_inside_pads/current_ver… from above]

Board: 2 copper layers, 4 parts (0 on the bottom side), 2 nets.
